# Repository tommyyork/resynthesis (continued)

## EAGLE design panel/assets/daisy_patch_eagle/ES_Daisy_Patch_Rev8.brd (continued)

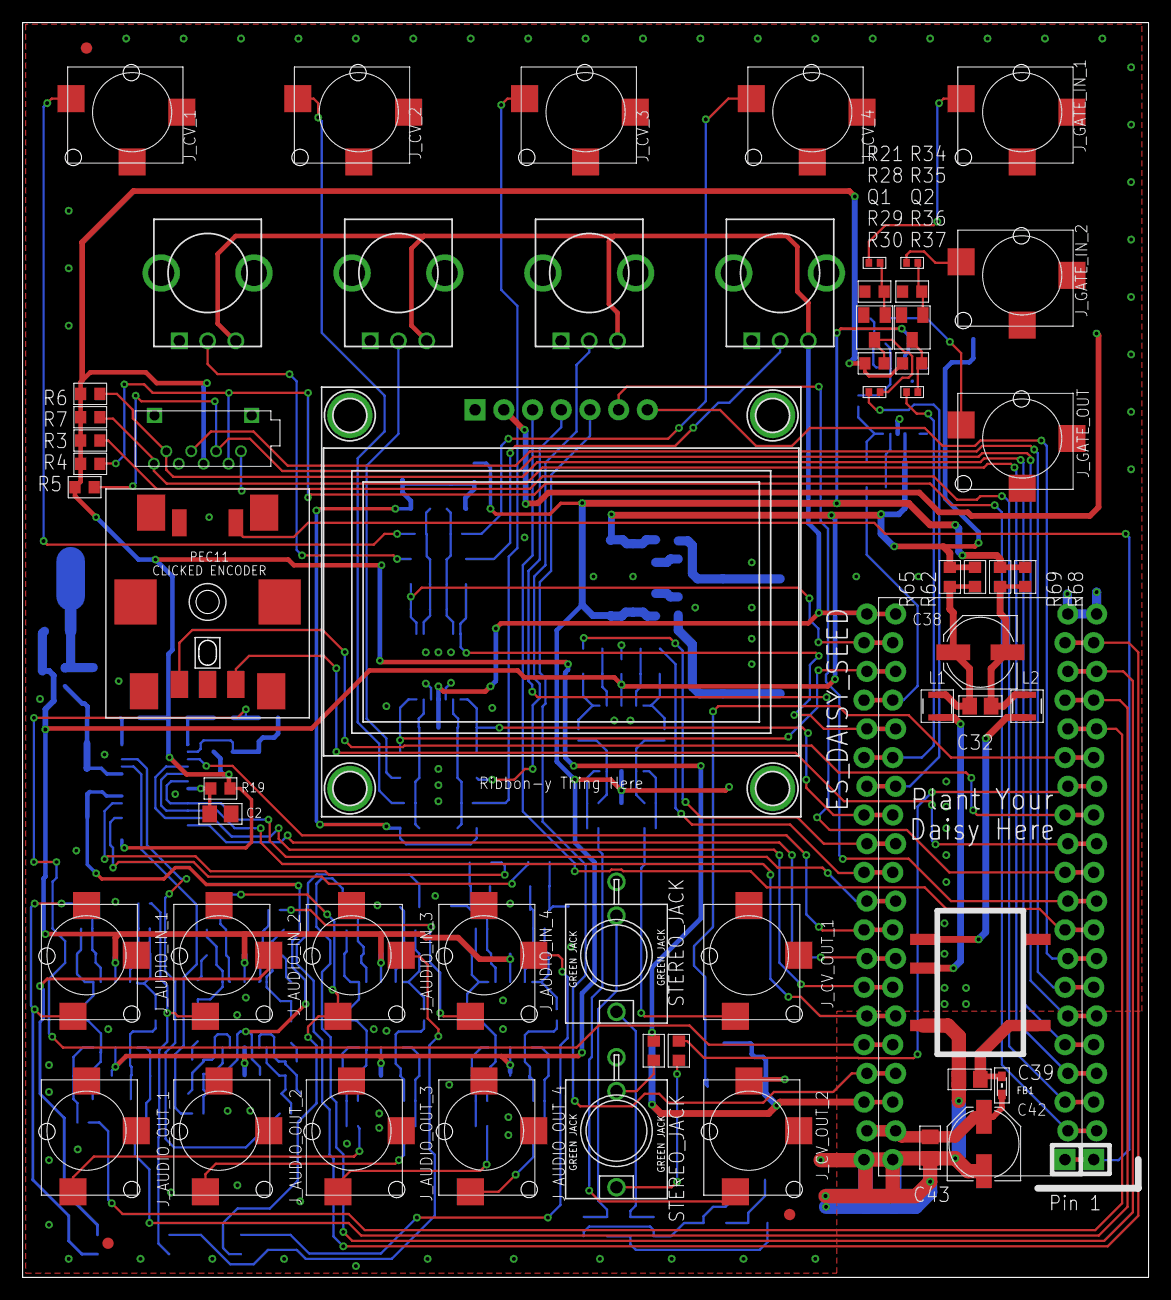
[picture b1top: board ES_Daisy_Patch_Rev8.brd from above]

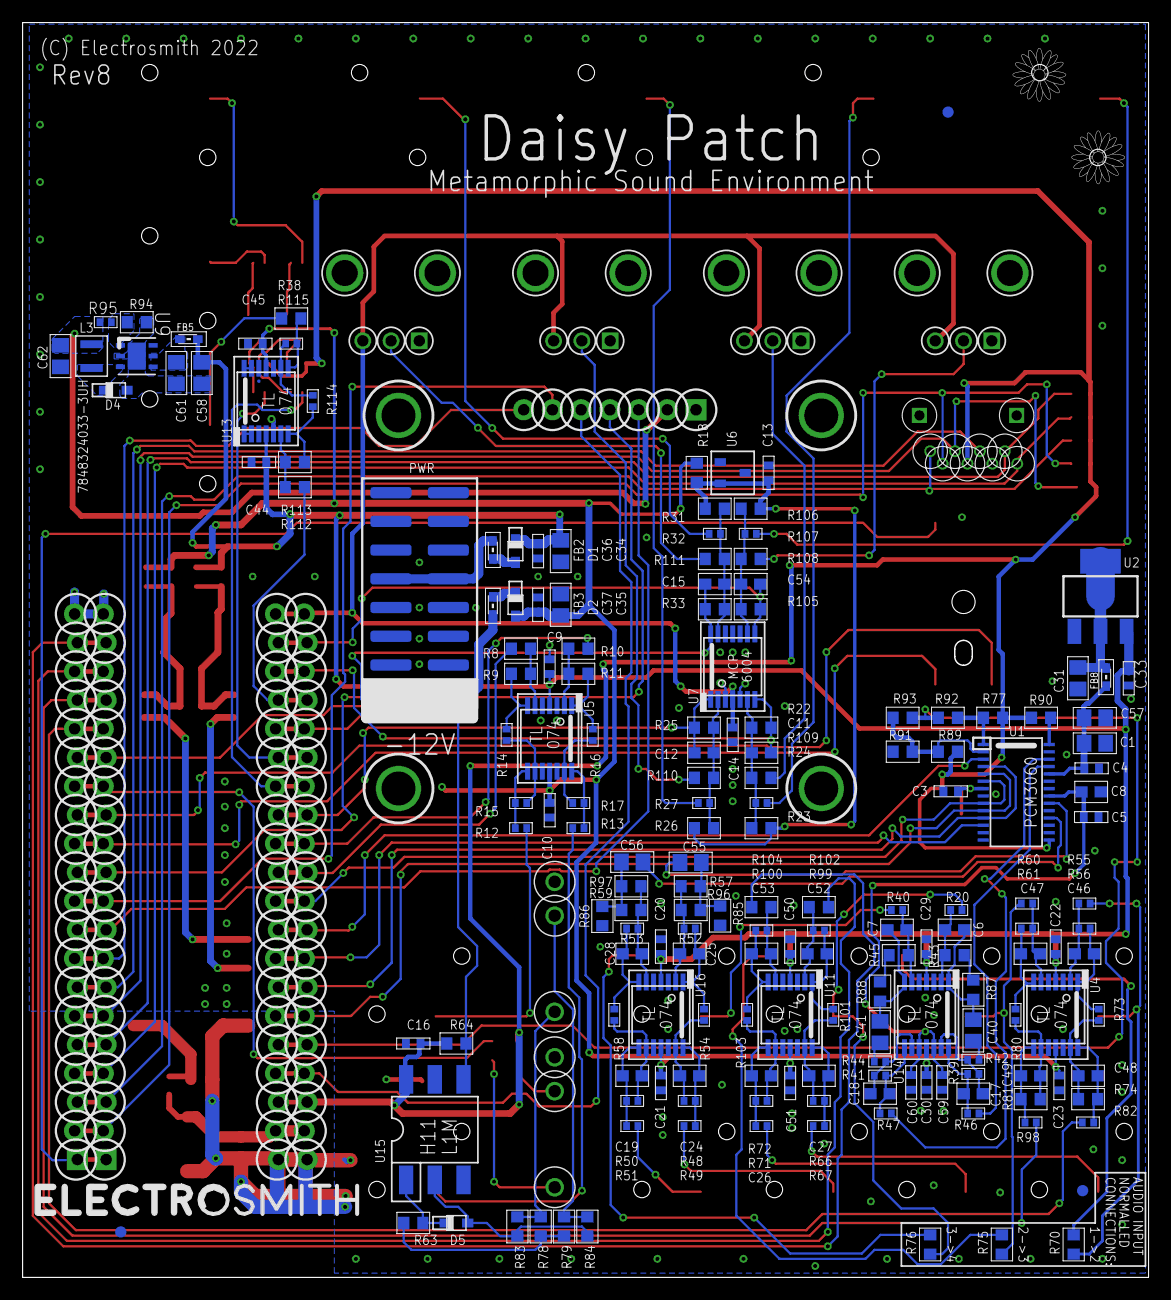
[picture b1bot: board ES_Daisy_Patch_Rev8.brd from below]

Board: 2 copper layers, 99.6 x 111.0 mm, 241 parts (179 on the bottom side), 157 nets.

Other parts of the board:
U$5, U$6: ES_DAISY_LOGO_1
U$7: ES_TEXT_3X30MM

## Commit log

2026-03-05 Resynthesis: adaptive smoothing, MAX COMP routing, and test updates
    - Raise the floor and reshape the CV_2 smoothing response so the panel’s 12 o’clock position is a musical “sweet spot”, concentrating the fastest/grittiest behaviour into the top of the control range.
    - Make magnitude smoothing adaptive to both spectral loudness and harmonic peakiness so dense, excited material automatically smooths into a cloud instead of abrasive static, while simpler inputs rem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
    - Add time‑stretch‑aware smoothing so extreme slow/fast `time_scale` settings get extra smoothing, reducing chatter in `_cv6_timestretch` and related MAX COMP examples without dulling normal operatio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
    -
2026-03-05 Resynthesis: refine sparsity, harmonic stack, and FLUFF renders
    - Tweak spectral sparsity shaping and band‑tilt so high CV values produce more animated, clustered textures while low values behave like gentle density shaping
    - Strengthen V/OCT harmonic scaffold, focusing, and level management so pitched use cases read more clearly without runaway gain
    - Add Makefile fluff target and retune FLUFF test defaults for smoother dynamics and more neutral baseline renders
    Made-with: Cursor
2026-03-05 fix to makefile.
2026-03-05 Resynthesis: retune smoothing and swap TIMESTRETCH/SMOOTH CVs
    Lower default magnitude smoothing to ~0.2, move TIMESTRETCH to CV_2 and SMOOTH to CV_6 across firmware, tests, docs, and panel generator so panel, CV sweeps, and block diagram stay in sync.
    Made-with: Cursor
2026-03-05 Resynthesis: add shifting block and align voct tests
    Add a Shifting front-end that pitch- and frequency-shifts input when PITCH LOCK is on, including a tracking high-pass just below the V/OCT fundamental, and document it in the block diagram and README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
    Made-with: Cursor
2026-03-05 Resynthesis: clarify offline tests and voct stack
    Tie the V/OCT harmonic-stack behaviour more tightly to pitch-locked mode so the requested fundamental dominates suggested-note analysis in the offline voct tests, while keeping the partial-based mode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
    Made-with: Cursor
2026-03-05 Note in the readme that this has moved more granular.
2026-03-06 Refactor - LLM may have screwed up the audio path.
2026-03-06 add taesg as inspiration.
2026-03-07 readme update.
2026-03-07 Panel: KiCad generator, mount slot cap, pattern boundary rules, Makefile
    - Add generate_panel_kicad.py: full KiCad PCB panel generator with three-zone
    pattern (A / morph / B), drill slots, footprints, copper pattern, silkscreen,
    solder mask, and Edge.Cuts. Uses PATTERN_EXTEND outside board and PCBWay DRC
    reference assets.
    - Cap mount drill slot height at 3 mm (MOUNT_SLOT_MAX_HEIGHT_MM); slot width
    unchanged; SD slot uncapped.
2026-03-07 Move pattern SVGs to panel/assets; update AGENT_SESSION.md
    - Relocate panel/pattern.svg, pattern_b.svg, pattern_c.svg to panel/assets/
    - Update generate_panel_kicad.py: PATTERN_SVG and PATTERN_B_SVG now point to
    HERE / 'assets' / 'pattern.svg' and HERE / 'assets' / 'pattern_c.svg'
    - AGENT_SESSION.md: add sections 25 (panel KiCad generator, mount slot cap,
    pattern boundary rules, Makefile) and 26 (SVG move and session log update)
    Made-with: Cursor
2026-03-07 Add kicad render.
2026-03-07 embed render.
2026-03-07 Another quick update.
2026-03-07 fix readme link.
2026-03-07 Last edit, then sleep.
2026-03-07 okay last.
2026-03-08 brand.
2026-03-08 Panel: label-avoiding pattern, bounce off mask, clip to panel, fab-safe output
    Background pattern (generate_panel_kicad.py):
    - Interpolate pattern toward no shape near text label boxes using the same
    easing as zone A→B morph (PATTERN_LABEL_FALLOFF_MM, smoothstep).
    - Terminal points: endpoints stop a random fraction before the label boundary
    (PATTERN_LABEL_TERMINAL_INSET_MIN/MAX) and emit a short arc away in a random
    direction (PATTERN_LABEL_ARC_AWAY_*) so lines do not meet at the center.
